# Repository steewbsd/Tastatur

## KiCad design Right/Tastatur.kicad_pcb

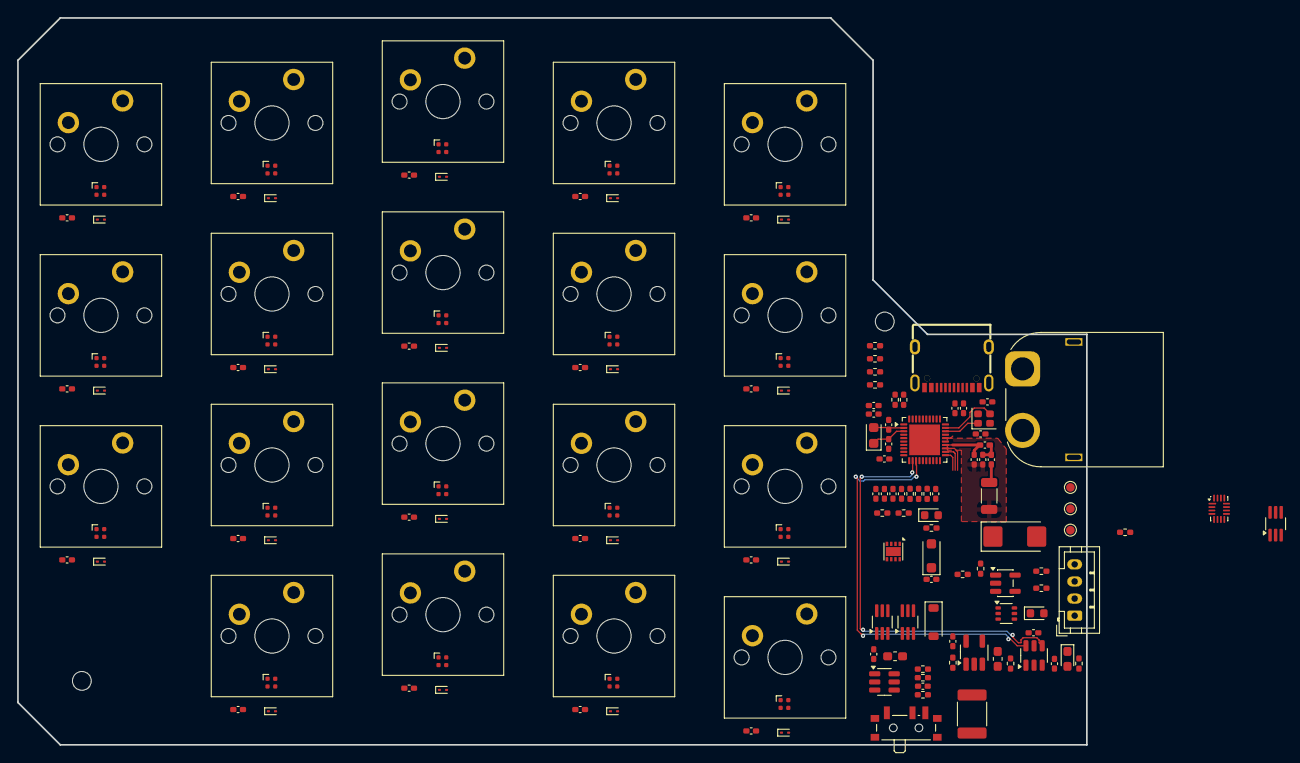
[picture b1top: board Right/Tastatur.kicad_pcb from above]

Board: 2 copper layers, 125.0 x 85.0 mm, 156 parts (1 on the bottom side), 103 nets.

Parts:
AE1: Antenna_Shield; L_1206_3216Metric
BT1: Battery_Cell; BatteryHolder_Keystone_1058_1x2032
C1, C37, C38, C39: 4u7; C_0402_1005Metric_Pad0.74x0.62mm_HandSolder
C2: 1u; C_0402_1005Metric_Pad0.74x0.62mm_HandSolder
C3: 100p; C_0402_1005Metric_Pad0.74x0.62mm_HandSolder
C4, C5, C14, C15, C16, C17, C18, C19, C20, C21, C22, C23, C24, C25, C26, C27, C28, C29, C30, C31, C32, C33, C34: 100n; C_0402_1005Metric_Pad0.74x0.62mm_HandSolder
C6, C9: 10p; C_0402_1005Metric_Pad0.74x0.62mm_HandSolder
C7, C8, C11: 22u; C_0402_1005Metric_Pad0.74x0.62mm_HandSolder
C10, C43: 10u; C_0402_1005Metric_Pad0.74x0.62mm_HandSolder
C13: 470u; CP_EIA-6032-28_Kemet-C_HandSolder
C35: 1p; C_0402_1005Metric_Pad0.74x0.62mm_HandSolder
C36: 802p; C_0402_1005Metric_Pad0.74x0.62mm_HandSolder
C40: 1p2; C_0402_1005Metric_Pad0.74x0.62mm_HandSolder
C41, C42: 12p; C_0402_1005Metric_Pad0.74x0.62mm_HandSolder
D1: CPDUR5V0HE-HF; D_0603_1608Metric_Pad1.05x0.95mm_HandSolder
D2: LMBR130T1G; D_SOD-123
D5: DDZ9678-7; D_SOD-123F
D6: RED; LED_0603_1608Metric
D7, D8, D9, D10, D11, D17, D18, D19, D20, D21, D27, D28, D29, D30, D31, D37, D38, D39, D40: SK6805-EC15; LED_SK6812_EC15_1.5x1.5mm
D12, D13, D14, D15, D16, D22, D23, D24, D25, D26, D32, D33, D34, D35, D36, D41, D42, D43, D44: RB521CS-30; D_SOD-923
D45: GREEN; LED_0603_1608Metric
F1: 1812L050/30PR; Fuse_1812_4532Metric_Pad1.30x3.40mm_HandSolder
H1, H2: MountingHole; MountingHole_2.2mm_M2_ISO7380
J1: Conn_01x04_Pin; JST_PH_B4B-PH-K_1x04_P2.00mm_Vertical
J3: XT60PW-M; AMASS_XT60PW-M_1x02_P7.20mm_Horizontal
L1: 4u7; L_0603_1608Metric_Pad1.05x0.95mm_HandSolder
L2: 120 Ohm @ 100 MHz; L_0603_1608Metric_Pad1.05x0.95mm_HandSolder
L3: 4n7; L_0402_1005Metric_Pad0.77x0.64mm_HandSolder
L4: 2n2; L_0402_1005Metric_Pad0.77x0.64mm_HandSolder
Q1, Q2, Q8: NTJD4152PT1G; SOT-363_SC-70-6_Handsoldering
Q3: Q_Dual_NMOS_S1G1D2S2G2D1; SOT-363_SC-70-6
R1, R25: 100R; R_0402_1005Metric_Pad0.72x0.64mm_HandSolder
R2, R10, R12: 50k; R_0402_1005Metric_Pad0.72x0.64mm_HandSolder
R3, R4: 5k1; R_0402_1005Metric_Pad0.72x0.64mm_HandSolder
R5, R28, R29: 0R; R_0402_1005Metric_Pad0.72x0.64mm_HandSolder
R6: 110k; R_0402_1005Metric_Pad0.72x0.64mm_HandSolder
R7: 15k; R_0402_1005Metric_Pad0.72x0.64mm_HandSolder
R13: 33k; R_0402_1005Metric_Pad0.72x0.64mm_HandSolder
R14: 51k; R_0402_1005Metric_Pad0.72x0.64mm_HandSolder
R15: 56k; R_0402_1005Metric_Pad0.72x0.64mm_HandSolder
R16, R17: 330R; R_0402_1005Metric_Pad0.72x0.64mm_HandSolder
R18: 20k; R_0402_1005Metric_Pad0.72x0.64mm_HandSolder
R21, R22, R23, R24: 500R; R_0402_1005Metric_Pad0.72x0.64mm_HandSolder
R26: 4k7; R_0402_1005Metric_Pad0.72x0.64mm_HandSolder
SW1: MK-12C02-G020; SW_SPDT_PCM12
SW2, SW3, SW4, SW5, SW6, SW7, SW8, SW9, SW10, SW11, SW12, SW13, SW14, SW15, SW16, SW17, SW18, SW19, SW20: SW_Push; SW_Cherry_MX_PCB_1.00u
TP1, TP2, TP3: TestPoint; TestPoint_Pad_D1.0mm
U1: USBLC6-2SC6; SOT-23-6
U2: TMUX1208RSV; UQFN-16_1.8x2.6mm_P0.4mm
U3: AP2112K-3.3; SOT-23-5_HandSoldering
U4: MT3608; SOT-23-6
U6: MCP73831-2-OT; SOT-23-5
U7: LM393; DFN-8-1EP_2x2mm_P0.5mm_EP1.05x1.75mm
U8: nRF52833_QDxx; QFN-40-1EP_5x5mm_P0.4mm_EP3.6x3.6mm
USB1: TYPE-C 16PIN 2MD(073); USB-C-SMD_TYPE-C-6PIN-2MD-073
Y1: 32MHz; Crystal_SMD_2016-4Pin_2.0x1.6mm
Y2: 32768 KHz; Crystal_SMD_2012-2Pin_2.0x1.2mm_HandSoldering

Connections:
+3V3: C1.2, C7.2, C13.1, C14.1, C38.2, C39.2, J1.2, L1.1, Q1.3 (D), Q1.6 (D), Q2.3 (D), R26.2, SW1.2 (C), U2.11 (VDD), U4.5 (IN), U8.8 (VDD), U8.9 (VDDH), U8.10 (VBUS), U8.18 (VDD), U8.30 (VDD), U8.40 (VDD)
+3V3BAT: Q1.1 (S), Q2.6 (D)
+3V3USB: C11.1, Q1.4 (S), Q3.1 (S), R12.2, TP3.1, U3.5 (VOUT)
+5V: C16.2, C17.2, C18.2, C19.2, C20.2, C21.2, C22.2, C23.2, C24.2, C25.2, C26.2, C27.2, C28.2, C29.2, C30.2, C31.2, C32.2, C33.2, C34.2, D7.4 (VDD), D8.4 (VDD), D9.4 (VDD), D10.4 (VDD), D11.4 (VDD), D17.4 (VDD), D18.4 (VDD), D19.4 (VDD), D20.4 (VDD), D21.4 (VDD), D27.4 (VDD), D28.4 (VDD), D29.4 (VDD), D30.4 (VDD), D31.4 (VDD), D37.4 (VDD), D38.4 (VDD), D39.4 (VDD), D40.4 (VDD), Q8.3 (D), Q8.6 (D)
+5VBAT: C8.2, D2.1 (K), Q8.1 (S), R6.1
+5VUSB: C43.2, F1.2, Q8.4 (S), R5.1, R16.1, TP2.1, U3.1 (VIN), U6.4 (V_{DD})
/COL0: SW2.1, SW7.1, SW12.1, U8.32 (AIN0/P0.02)
/COL1: SW3.1, SW8.1, SW13.1, SW17.1, U8.31 (AIN1/P0.03)
/COL2: SW4.1, SW9.1, SW14.1, SW18.1, U8.4 (AIN2/P0.04)
/COL3: SW5.1, SW10.1, SW15.1, SW19.1, U8.5 (AIN3/P0.05)
/COL4: SW6.1, SW11.1, SW16.1, SW20.1, U8.7 (P0.11)
/D+: U1.6 (I/O1), U8.13 (D+)
/D-: U1.4 (I/O2), U8.12 (D-)
/ED+: U1.1 (I/O1), USB1.6 (DP1), USB1.8 (DP2)
/ED-: U1.3 (I/O2), USB1.5 (DN2), USB1.7 (DN1)
/LD0: R21.1, U2.2 (S1)
/LD1: R22.1, U2.3 (S2)
/LD2: R23.1, U2.4 (S3)
/LD3: R24.1, U2.5 (S4)
/LEDDATA: U2.6 (D), U8.6 (P1.09)
/LEDSEL0: U2.15 (A0), U8.22 (NFC1/P0.09)
/LEDSEL1: U2.14 (A1), U8.23 (NFC2/P0.10)
/LEDTOGGLE: R2.1, SW1.1 (B), U2.16 (EN), U4.4 (EN)
/ROW0: D12.1 (K), D13.1 (K), D14.1 (K), D15.1 (K), D16.1 (K), U8.14 (P0.15)
/ROW1: D22.1 (K), D23.1 (K), D24.1 (K), D25.1 (K), D26.1 (K), U8.15 (P0.17)
/ROW2: D32.1 (K), D33.1 (K), D34.1 (K), D35.1 (K), D36.1 (K), U8.17 (P0.20)
/ROW3: D41.1 (K), D42.1 (K), D43.1 (K), D44.1 (K), U8.33 (AIN4/P0.28)
/VBAT: BT1.1 (+), C15.1, Q2.1 (S), Q3.2 (G), R10.2, R12.1, R13.1, R14.1, U6.3 (V_{BAT}), U7.8 (V+)
/VBUS: D1.2 (A2), L2.1, U1.5 (VBUS), USB1.2 (VBUS), USB1.11 (VBUS)
/mcu/SWDCLK: J1.4, R1.1
/mcu/SWDIO: J1.3, R25.1
GND: AE1.2 (Shield), BT1.2 (-), C1.1, C2.1, C3.1, C4.2, C5.1, C6.2, C7.1, C8.1, C9.2, C10.2, C11.2, C13.2, C14.2, C15.2, C16.1, C17.1, C18.1, C19.1, C20.1, C21.1, C22.1, C23.1, C24.1, C25.1, C26.1, C27.1, C28.1, C29.1, C30.1, C31.1, C32.1, C33.1, C34.1, C35.2, C36.1, C37.1, C38.1, C39.1, C40.2, C41.1, C42.1, C43.1, D1.1 (A1), D5.2 (A), D6.1 (K), D7.2 (VSS), D8.2 (VSS), D9.2 (VSS), D10.2 (VSS), D11.2 (VSS), D17.2 (VSS), D18.2 (VSS), D19.2 (VSS), D20.2 (VSS), D21.2 (VSS), D27.2 (VSS), D28.2 (VSS), D29.2 (VSS), D30.2 (VSS), D31.2 (VSS), D37.2 (VSS), D38.2 (VSS), D39.2 (VSS), D40.2 (VSS), J1.1, J3.2, Q1.2 (G), Q1.5 (G), Q2.5 (G), Q8.2 (G), Q8.5 (G), R2.2, R3.2, R4.2, R7.2, R15.2, R18.2, R28.2, R29.2, SW1.3 (A), TP1.1, U1.2 (GND), U2.1 (VSS), U2.12 (GND), U3.2 (GND), U4.2 (GND), U6.2 (V_{SS}), U7.4 (V-), U7.5 (+), U8.25 (VSS_PA), U8.37 (VSS), U8.41 (VSS), USB1.1 (GND), USB1.12 (GND), USB1.13 (SHELL), USB1.14 (SHELL), Y1.2, Y1.4
unnamed: AE1.1 (A), L4.1
unnamed: C10.1, F1.1, L2.2
unnamed: C40.1, L3.1, L4.2
unnamed: D2.2 (A), L1.2, U4.1 (SW)
unnamed: D5.1 (K), R14.2, U7.2 (-)
unnamed: D6.2 (A), R17.2
unnamed: D7.3 (DIN), R21.2
unnamed: D7.1 (DOUT), D8.3 (DIN)
unnamed: D8.1 (DOUT), D9.3 (DIN)
unnamed: D9.1 (DOUT), D10.3 (DIN)
unnamed: D10.1 (DOUT), D11.3 (DIN)
unnamed: D12.2 (A), SW2.2
unnamed: D13.2 (A), SW3.2
unnamed: D14.2 (A), SW4.2
unnamed: D15.2 (A), SW5.2
unnamed: D16.2 (A), SW6.2
unnamed: D17.3 (DIN), R22.2
unnamed: D17.1 (DOUT), D18.3 (DIN)
unnamed: D18.1 (DOUT), D19.3 (DIN)
unnamed: D19.1 (DOUT), D20.3 (DIN)
unnamed: D20.1 (DOUT), D21.3 (DIN)
unnamed: D22.2 (A), SW7.2
unnamed: D23.2 (A), SW8.2
unnamed: D24.2 (A), SW9.2
unnamed: D25.2 (A), SW10.2
unnamed: D26.2 (A), SW11.2
unnamed: D27.3 (DIN), R23.2
unnamed: D27.1 (DOUT), D28.3 (DIN)
unnamed: D28.1 (DOUT), D29.3 (DIN)
unnamed: D29.1 (DOUT), D30.3 (DIN)
unnamed: D30.1 (DOUT), D31.3 (DIN)
unnamed: D32.2 (A), SW12.2
unnamed: D33.2 (A), SW13.2
unnamed: D34.2 (A), SW14.2
unnamed: D35.2 (A), SW15.2
unnamed: D36.2 (A), SW16.2
unnamed: D37.3 (DIN), R24.2
unnamed: D37.1 (DOUT), D38.3 (DIN)
unnamed: D38.1 (DOUT), D39.3 (DIN)
unnamed: D39.1 (DOUT), D40.3 (DIN)
unnamed: D41.2 (A), SW17.2
unnamed: D42.2 (A), SW18.2
unnamed: D43.2 (A), SW19.2
unnamed: D44.2 (A), SW20.2
unnamed: D45.2 (A), R16.2
unnamed: D45.1 (K), U6.1 (STAT)
unnamed: J3.1, Q2.4 (S)
unnamed: Q2.2 (G), Q3.6 (D), R10.1
unnamed: R17.1, U7.1
unnamed: R5.2, U3.3 (EN)
unnamed: R6.2, R7.1, U4.3 (FB)
unnamed: R18.1, U6.5 (PROG)
unnamed: R13.2, R15.1, U7.3 (+)
unnamed: U7.6 (-), U7.7
unnamed: R29.1, U8.35 (AIN6/P0.30)
unnamed: R28.1, U8.36 (AIN7/P0.31)
unnamed: C35.1, L3.2, U8.24 (ANT)
unnamed: C5.2, U8.1 (DEC1)
unnamed: C3.2, U8.27 (DEC3)
unnamed: C2.2, U8.26 (DEC6), U8.38 (DEC4)
unnamed: C36.2, U8.21 (DEC5)
unnamed: C37.2, U8.11 (DECUSB)
unnamed: C4.1, R26.1, U8.16 (P0.18/~RESET)
unnamed: R1.2, U8.20 (SWDCLK)
unnamed: R25.2, U8.19 (SWDIO)
unnamed: C6.1, U8.28 (XC1), Y1.1
unnamed: C9.1, U8.29 (XC2), Y1.3
unnamed: C41.2, U8.2 (XL1/P0.00), Y2.2
unnamed: C42.2, U8.3 (XL2/P0.01), Y2.1
unnamed: R4.1, USB1.4 (CC1)
unnamed: R3.1, USB1.10 (CC2)

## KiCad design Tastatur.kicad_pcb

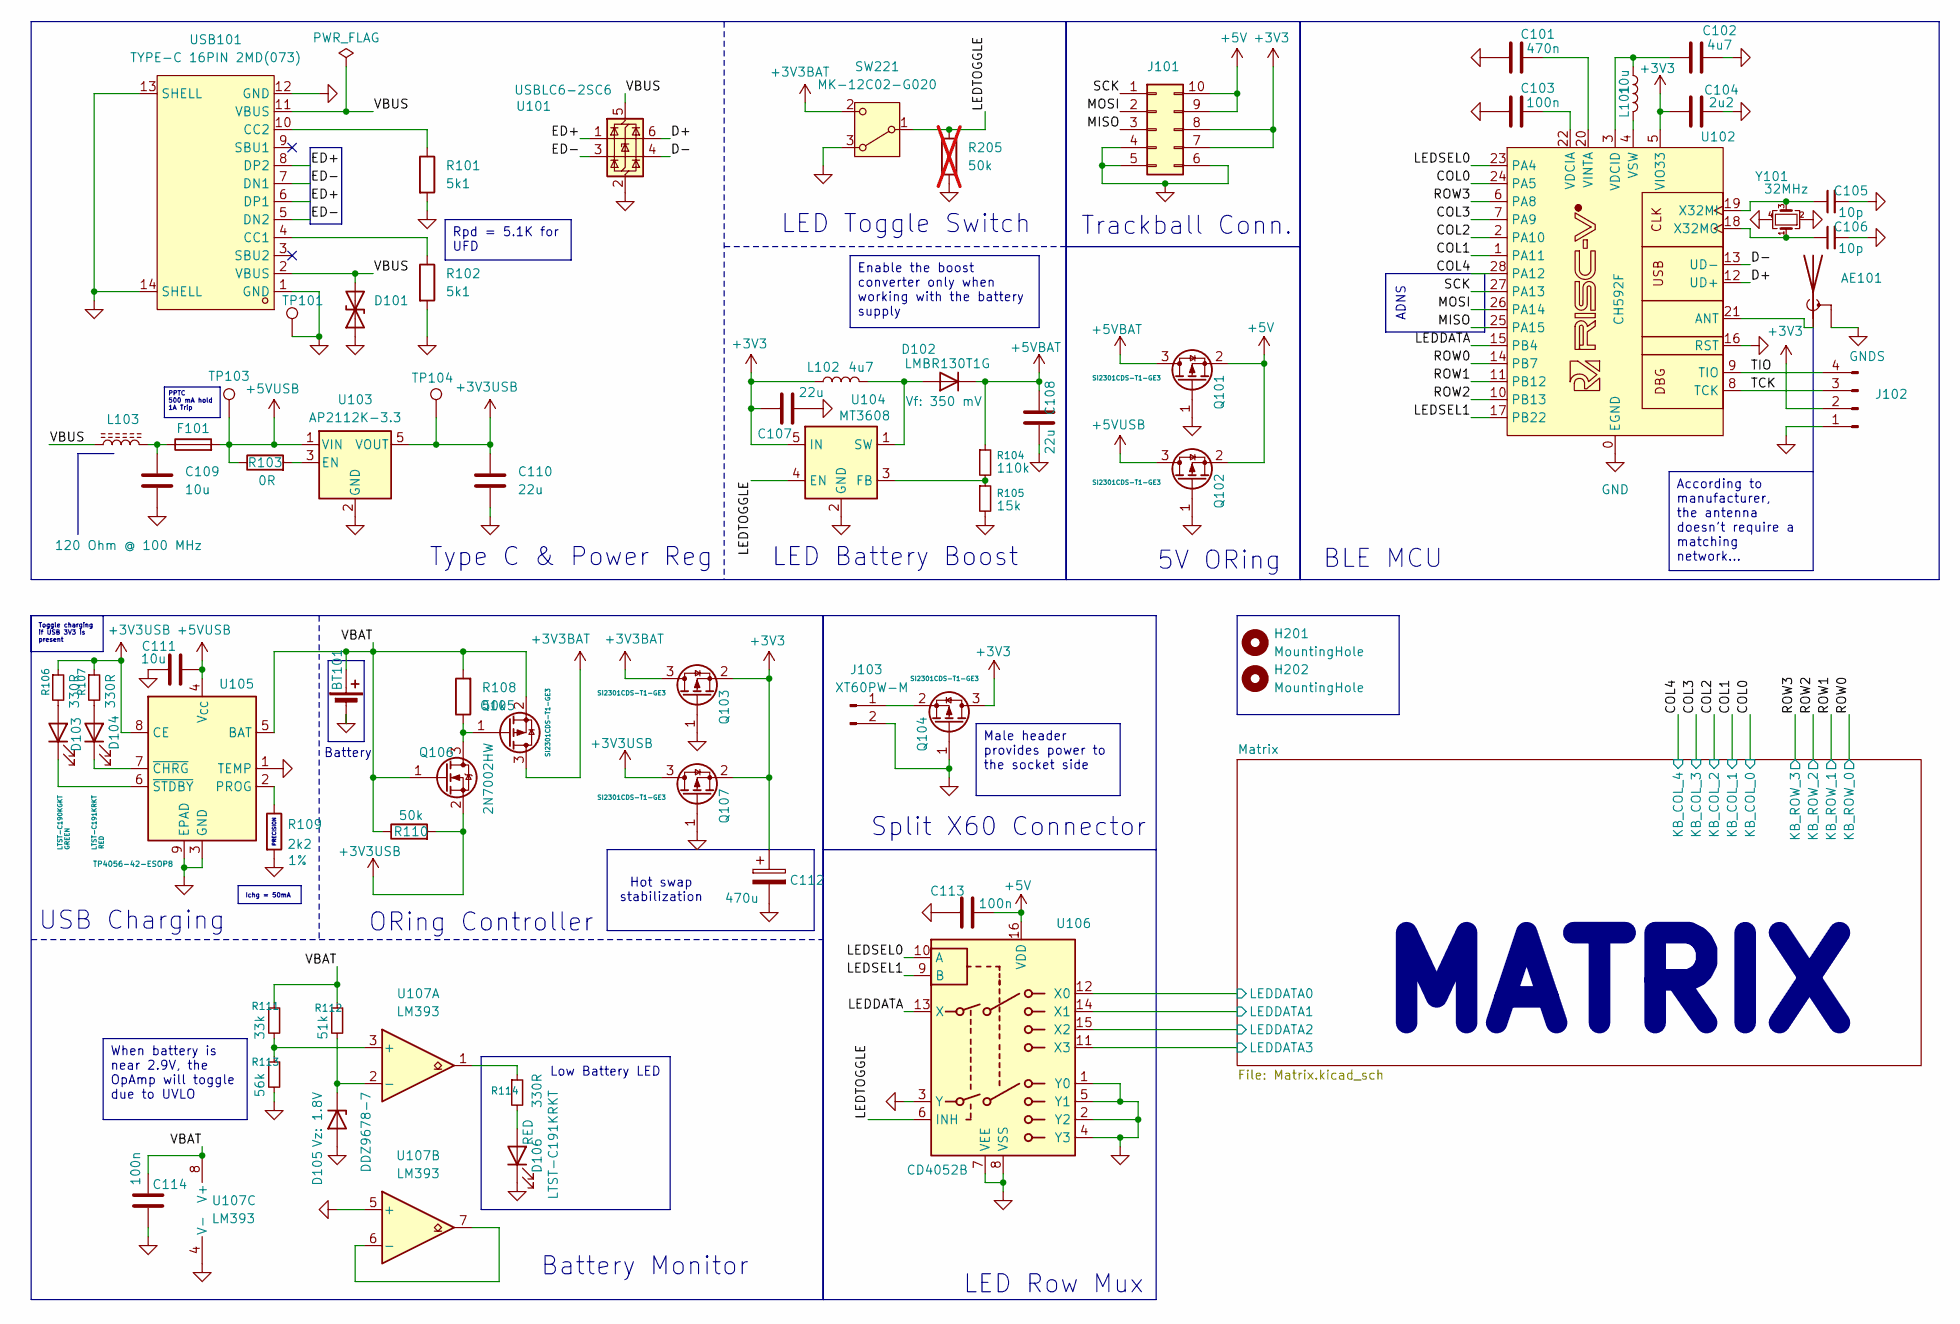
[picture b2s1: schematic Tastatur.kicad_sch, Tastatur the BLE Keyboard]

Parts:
AE101: Antenna_Shield; L_1206_3216Metric
BT101: Battery_Cell; BatteryHolder_Keystone_1058_1x2032
C101: 470n; C_0603_1608Metric_Pad1.08x0.95mm_HandSolder
C102: 4u7; C_0603_1608Metric_Pad1.08x0.95mm_HandSolder
C103, C113, C114: 100n; C_0603_1608Metric_Pad1.08x0.95mm_HandSolder
C104: 2u2; C_0603_1608Metric_Pad1.08x0.95mm_HandSolder
C105, C106: 10p; C_0603_1608Metric_Pad1.08x0.95mm_HandSolder
C107, C108, C110: 22u; C_0603_1608Metric_Pad1.08x0.95mm_HandSolder
C109, C111: 10u; C_0603_1608Metric_Pad1.08x0.95mm_HandSolder
C112: 470u; CP_Elec_6.3x7.7
D101: CPDUR5V0HE-HF; D_0603_1608Metric_Pad1.05x0.95mm_HandSolder
D102: LMBR130T1G; D_SOD-123
D103: GREEN; LED_0603_1608Metric
D104, D106: RED; LED_0603_1608Metric
D105: DDZ9678-7; D_SOD-123F
F101: 1812L050/30PR; Fuse_1812_4532Metric_Pad1.30x3.40mm_HandSolder
H201, H202: MountingHole; MountingHole_2.2mm_M2_ISO7380
J101: Conn_02x05_Counter_Clockwise
J102: Conn_01x04_Pin; JST_PH_B4B-PH-K_1x04_P2.00mm_Vertical
J103: XT60PW-M; AMASS_XT60PW-M_1x02_P7.20mm_Horizontal
L101: 10u; L_0603_1608Metric_Pad1.05x0.95mm_HandSolder
L102: 4u7; L_0603_1608Metric_Pad1.05x0.95mm_HandSolder
L103: 120 Ohm @ 100 MHz; L_0603_1608Metric_Pad1.05x0.95mm_HandSolder
Q101, Q102, Q103, Q104, Q105, Q107: SI2301CDS-T1-GE3; SOT-23_Handsoldering
Q106: 2N7002HW; SOT-323_SC-70_Handsoldering
R101, R102: 5k1; R_0603_1608Metric_Pad0.98x0.95mm_HandSolder
R103: 0R; R_0603_1608Metric_Pad0.98x0.95mm_HandSolder
R104: 110k; R_0603_1608Metric_Pad0.98x0.95mm_HandSolder
R105: 15k; R_0603_1608Metric_Pad0.98x0.95mm_HandSolder
R106, R107, R114: 330R; R_0603_1608Metric_Pad0.98x0.95mm_HandSolder
R108, R110: 50k; R_0603_1608Metric_Pad0.98x0.95mm_HandSolder
R109: 2k2; R_0603_1608Metric_Pad0.98x0.95mm_HandSolder; Tolerance 1%
R111: 33k; R_0603_1608Metric_Pad0.98x0.95mm_HandSolder
R112: 51k; R_0603_1608Metric_Pad0.98x0.95mm_HandSolder
R113: 56k; R_0603_1608Metric_Pad0.98x0.95mm_HandSolder
R205: 50k; R_0603_1608Metric_Pad0.98x0.95mm_HandSolder; not fitted
SW221: MK-12C02-G020; SW_SPDT_PCM12
TP101, TP103, TP104: TestPoint; TestPoint_Pad_D1.0mm
U101: USBLC6-2SC6; SOT-23-6
U102: CH592F
U103: AP2112K-3.3; SOT-23-5_HandSoldering
U104: MT3608; SOT-23-6
U105: TP4056-42-ESOP8; SOP-8-1EP_4.57x4.57mm_P1.27mm_EP4.57x4.45mm
U106: CD4052B; TSSOP-16_4.4x5mm_P0.65mm
U107: LM393; SOIC-8_3.9x4.9mm_P1.27mm
USB101: TYPE-C 16PIN 2MD(073); USB-C-SMD_TYPE-C-6PIN-2MD-073; LCSC Part C2765186
Y101: 32MHz; Crystal_SMD_2016-4Pin_2.0x1.6mm

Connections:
+3V3: C104.1, C107.2, C112.1, J101.7, J101.8, J102.2, L102.1, Q103.2 (S), Q104.3 (D), Q107.2 (S), U102.5 (VIO33), U104.5 (IN)
+3V3BAT: Q103.3 (D), Q105.3 (D), SW221.2 (C)
+3V3USB: C110.1, Q106.2 (S), Q107.3 (D), R106.1, R107.1, R110.2, TP104.1, U103.5 (VOUT), U105.8 (CE)
+5V: C113.1, J101.9, J101.10, Q101.2 (S), Q102.2 (S), U106.16 (VDD); also elsewhere on the board
+5VBAT: C108.2, D102.1 (K), Q101.3 (D), R104.1
+5VUSB: C111.2, F101.2, Q102.3 (D), R103.1, TP103.1, U103.1 (VIN), U105.4 (V_{CC})
/COL0: U102.24 (PA5); also elsewhere on the board
/COL1: U102.1 (PA11); also elsewhere on the board
/COL2: U102.2 (PA10); also elsewhere on the board
/COL3: U102.7 (PA9); also elsewhere on the board
/COL4: U102.28 (PA12); also elsewhere on the board
/D+: U101.6 (I/O1), U102.12 (UD+)
/D-: U101.4 (I/O2), U102.13 (UD-)
/ED+: U101.1 (I/O1), USB101.6 (DP1), USB101.8 (DP2)
/ED-: U101.3 (I/O2), USB101.5 (DN2), USB101.7 (DN1)
/LEDDATA: U102.15 (PB4), U106.13 (X)
/LEDSEL0: U102.23 (PA4), U106.10 (A)
/LEDSEL1: U102.17 (PB22), U106.9 (B)
/LEDTOGGLE: R205.1, SW221.1 (B), U104.4 (EN), U106.6 (INH)
/MISO: J101.3, U102.25 (PA15)
/MOSI: J101.2, U102.26 (PA14)
/Matrix/LEDDATA0: U106.12 (X0); also elsewhere on the board
/Matrix/LEDDATA1: U106.14 (X1); also elsewhere on the board
/Matrix/LEDDATA2: U106.15 (X2); also elsewhere on the board
/Matrix/LEDDATA3: U106.11 (X3); also elsewhere on the board
/ROW0: U102.14 (PB7); also elsewhere on the board
/ROW1: U102.11 (PB12); also elsewhere on the board
/ROW2: U102.10 (PB13); also elsewhere on the board
/ROW3: U102.6 (PA8); also elsewhere on the board
/SCK: J101.1, U102.27 (PA13)
/TCK: J102.3, U102.8 (TCK)
/TIO: J102.4, U102.9 (TIO)
/VBAT: BT101.1 (+), C114.1, Q105.2 (S), Q106.1 (G), R108.2, R110.1, R111.1, R112.1, U105.5 (BAT), U107.8 (V+)
/VBUS: D101.2 (A2), L103.1, U101.5 (VBUS), USB101.2 (VBUS), USB101.11 (VBUS)
GND: BT101.2 (-), C101.1, C102.2, C103.1, C104.2, C105.2, C106.2, C107.1, C108.1, C109.2, C110.2, C111.1, C112.2, C113.2, C114.2, D101.1 (A1), D105.2 (A), D106.1 (K), J101.4, J101.5, J101.6, J102.1, J103.2, Q101.1 (G), Q102.1 (G), Q103.1 (G), Q104.1 (G), Q107.1 (G), R101.2, R102.2, R105.2, R109.2, R113.2, R205.2, SW221.3 (A), TP101.1, U101.2 (GND), U102.0 (EGND), U102.16 (RST), U103.2 (GND), U104.2 (GND), U105.1 (TEMP), U105.3 (GND), U105.9 (EPAD), U106.1 (Y0), U106.2 (Y2), U106.3 (Y), U106.4 (Y3), U106.5 (Y1), U106.7 (VEE), U106.8 (VSS), U107.4 (V-), U107.5 (+), USB101.1 (GND), USB101.12 (GND), USB101.13 (SHELL), USB101.14 (SHELL), Y101.2, Y101.4; also elsewhere on the board
GNDS: AE101.2 (Shield)
unnamed: AE101.1 (A), U102.21 (ANT)
unnamed: C109.1, F101.1, L103.2
unnamed: D102.2 (A), L102.2, U104.1 (SW)
unnamed: D103.2 (A), R106.2
unnamed: D103.1 (K), U105.6 (~STDBY)
unnamed: D104.2 (A), R107.2
unnamed: D104.1 (K), U105.7 (~CHRG)
unnamed: D105.1 (K), R112.2, U107.2 (-)
unnamed: D106.2 (A), R114.2
unnamed: J103.1, Q104.2 (S)
unnamed: Q105.1 (G), Q106.3 (D), R108.1
unnamed: R114.1, U107.1
unnamed: C103.2, U102.22 (VDCIA)
unnamed: C102.1, L101.1, U102.3 (VDCID)
unnamed: C101.2, U102.20 (VINTA)
unnamed: L101.2, U102.4 (VSW)
unnamed: C105.1, U102.19 (X32MI), Y101.3
unnamed: C106.1, U102.18 (X32MO), Y101.1
unnamed: R103.2, U103.3 (EN)
unnamed: R104.2, R105.1, U104.3 (FB)
unnamed: R109.1, U105.2 (PROG)
unnamed: R111.2, R113.1, U107.3 (+)
unnamed: U107.6 (-), U107.7
unnamed: R102.1, USB101.4 (CC1)
unnamed: R101.1, USB101.10 (CC2)

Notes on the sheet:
LED Toggle Switch
Hot swap stabilization
MATRIX
PRECISION
Low Battery LED
5V ORing
USB Charging
BLE MCU
Battery
ADNS
Split X60 Connector
Battery Monitor
ORing Controller
Trackball Conn.
LED Battery Boost
Type C & Power Reg
LED Row Mux
According to manufacturer, the antenna doesn't require a matching network...
Ichg = 50mA
PPTC 500 mA hold 1A Trip
Toggle charging if USB 3V3 is present
When battery is near 2.9V, the OpAmp will toggle due to UVLO
Enable the boost converter only when working with the battery supply
Male header provides power to the socket side
Rpd = 5.1K for UFD

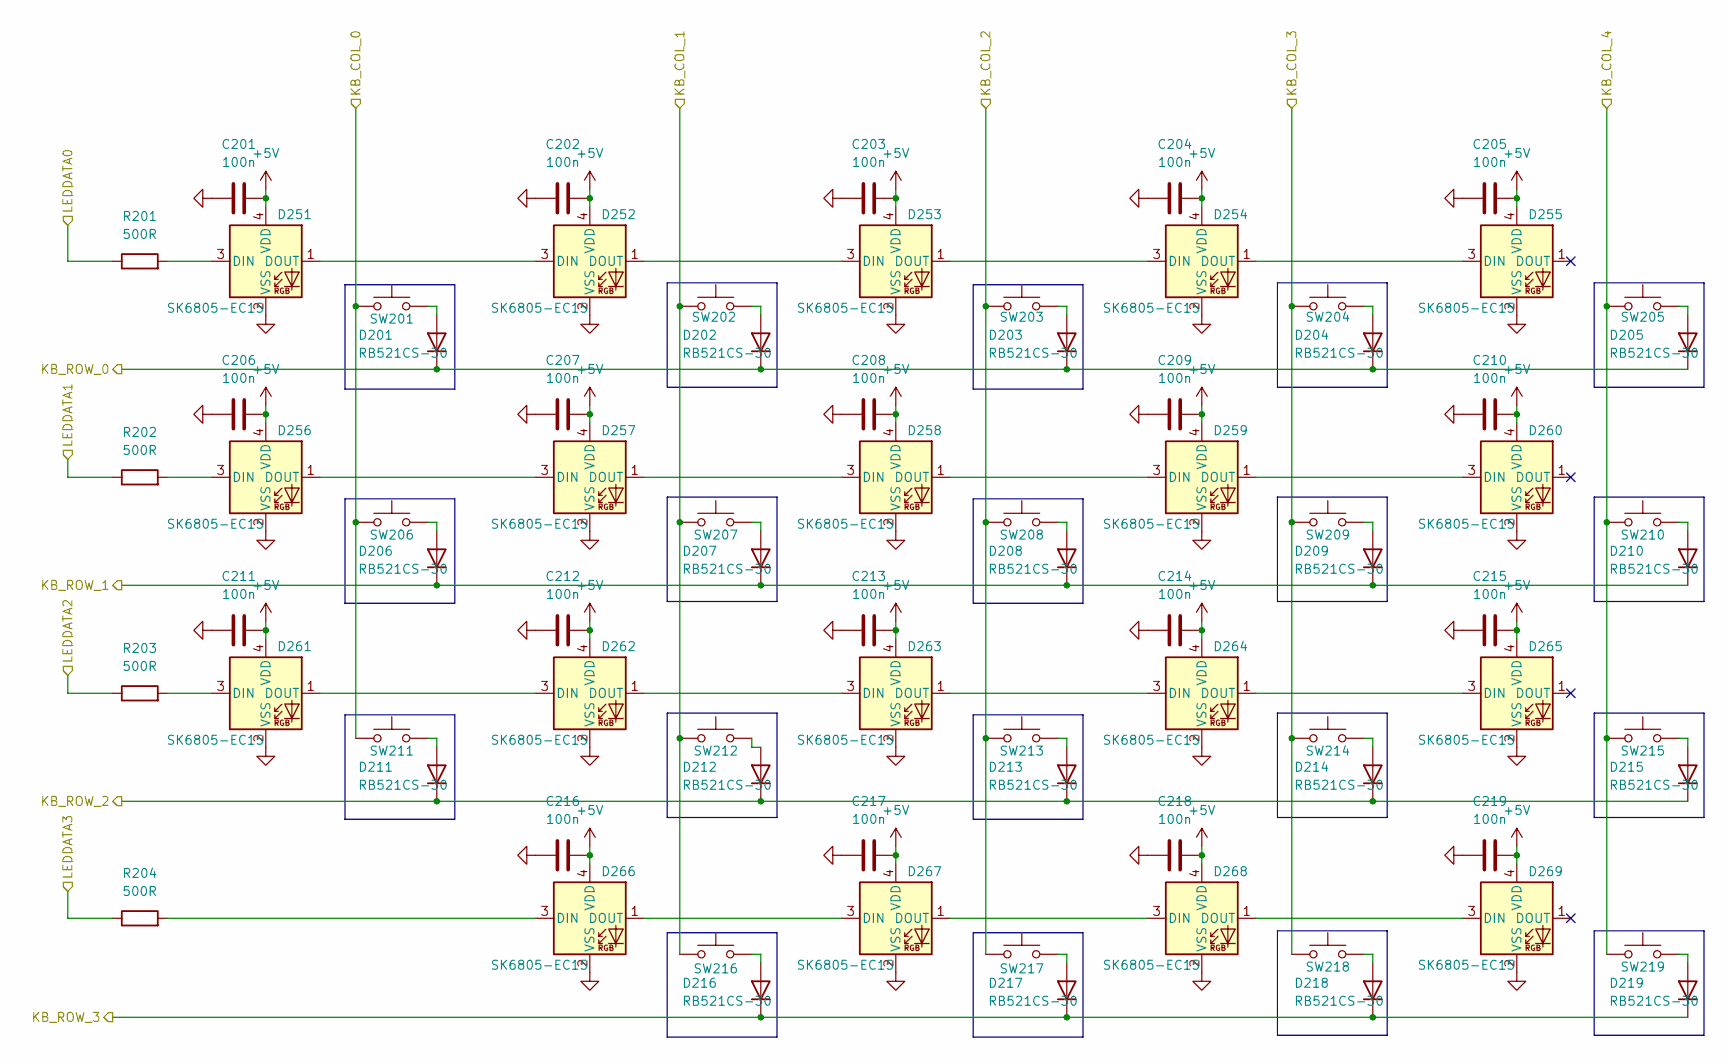
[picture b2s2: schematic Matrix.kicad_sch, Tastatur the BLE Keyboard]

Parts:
C201, C202, C203, C204, C205, C206, C207, C208, C209, C210, C211, C212, C213, C214, C215, C216, C217, C218, C219: 100n; C_0603_1608Metric_Pad1.08x0.95mm_HandSolder
D201, D202, D203, D204, D205, D206, D207, D208, D209, D210, D211, D212, D213, D214, D215, D216, D217, D218, D219: RB521CS-30; D_SOD-923
D251, D252, D253, D254, D255, D256, D257, D258, D259, D260, D261, D262, D263, D264, D265, D266, D267, D268, D269: SK6805-EC15; LED_SK6812_EC15_1.5x1.5mm; LCSC C2890035
R201, R202, R203, R204: 500R; R_0603_1608Metric_Pad0.98x0.95mm_HandSolder
SW201, SW202, SW203, SW204, SW205, SW206, SW207, SW208, SW209, SW210, SW211, SW212, SW213, SW214, SW215, SW216, SW217, SW218, SW219: SW_Push; SW_Cherry_MX_PCB_1.00u

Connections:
+5V: C201.2, C202.2, C203.2, C204.2, C205.2, C206.2, C207.2, C208.2, C209.2, C210.2, C211.2, C212.2, C213.2, C214.2, C215.2, C216.2, C217.2, C218.2, C219.2, D251.4 (VDD), D252.4 (VDD), D253.4 (VDD), D254.4 (VDD), D255.4 (VDD), D256.4 (VDD), D257.4 (VDD), D258.4 (VDD), D259.4 (VDD), D260.4 (VDD), D261.4 (VDD), D262.4 (VDD), D263.4 (VDD), D264.4 (VDD), D265.4 (VDD), D266.4 (VDD), D267.4 (VDD), D268.4 (VDD), D269.4 (VDD); also elsewhere on the board
/COL0: SW201.1, SW206.1, SW211.1; also elsewhere on the board
/COL1: SW202.1, SW207.1, SW212.1, SW216.1; also elsewhere on the board
/COL2: SW203.1, SW208.1, SW213.1, SW217.1; also elsewhere on the board
/COL3: SW204.1, SW209.1, SW214.1, SW218.1; also elsewhere on the board
/COL4: SW205.1, SW210.1, SW215.1, SW219.1; also elsewhere on the board
/Matrix/LEDDATA0: R201.1; also elsewhere on the board
/Matrix/LEDDATA1: R202.1; also elsewhere on the board
/Matrix/LEDDATA2: R203.1; also elsewhere on the board
/Matrix/LEDDATA3: R204.1; also elsewhere on the board
/ROW0: D201.1 (K), D202.1 (K), D203.1 (K), D204.1 (K), D205.1 (K); also elsewhere on the board
/ROW1: D206.1 (K), D207.1 (K), D208.1 (K), D209.1 (K), D210.1 (K); also elsewhere on the board
/ROW2: D211.1 (K), D212.1 (K), D213.1 (K), D214.1 (K), D215.1 (K); also elsewhere on the board
/ROW3: D216.1 (K), D217.1 (K), D218.1 (K), D219.1 (K); also elsewhere on the board
GND: C201.1, C202.1, C203.1, C204.1, C205.1, C206.1, C207.1, C208.1, C209.1, C210.1, C211.1, C212.1, C213.1, C214.1, C215.1, C216.1, C217.1, C218.1, C219.1, D251.2 (VSS), D252.2 (VSS), D253.2 (VSS), D254.2 (VSS), D255.2 (VSS), D256.2 (VSS), D257.2 (VSS), D258.2 (VSS), D259.2 (VSS), D260.2 (VSS), D261.2 (VSS), D262.2 (VSS), D263.2 (VSS), D264.2 (VSS), D265.2 (VSS), D266.2 (VSS), D267.2 (VSS), D268.2 (VSS), D269.2 (VSS); also elsewhere on the board
unnamed: D201.2 (A), SW201.2
unnamed: D202.2 (A), SW202.2
unnamed: D203.2 (A), SW203.2
unnamed: D204.2 (A), SW204.2
unnamed: D205.2 (A), SW205.2
unnamed: D206.2 (A), SW206.2
unnamed: D207.2 (A), SW207.2
unnamed: D208.2 (A), SW208.2
unnamed: D209.2 (A), SW209.2
unnamed: D210.2 (A), SW210.2
unnamed: D211.2 (A), SW211.2
unnamed: D212.2 (A), SW212.2
unnamed: D213.2 (A), SW213.2
unnamed: D214.2 (A), SW214.2
unnamed: D215.2 (A), SW215.2
unnamed: D216.2 (A), SW216.2
unnamed: D217.2 (A), SW217.2
unnamed: D218.2 (A), SW218.2
unnamed: D219.2 (A), SW219.2
unnamed: D251.3 (DIN), R201.2
unnamed: D251.1 (DOUT), D252.3 (DIN)
unnamed: D252.1 (DOUT), D253.3 (DIN)
unnamed: D253.1 (DOUT), D254.3 (DIN)
unnamed: D254.1 (DOUT), D255.3 (DIN)
unnamed: D256.3 (DIN), R202.2
unnamed: D256.1 (DOUT), D257.3 (DIN)
unnamed: D257.1 (DOUT), D258.3 (DIN)
unnamed: D258.1 (DOUT), D259.3 (DIN)
unnamed: D259.1 (DOUT), D260.3 (DIN)
unnamed: D261.3 (DIN), R203.2
unnamed: D261.1 (DOUT), D262.3 (DIN)
unnamed: D262.1 (DOUT), D263.3 (DIN)
unnamed: D263.1 (DOUT), D264.3 (DIN)
unnamed: D264.1 (DOUT), D265.3 (DIN)
unnamed: D266.3 (DIN), R204.2
unnamed: D266.1 (DOUT), D267.3 (DIN)
unnamed: D267.1 (DOUT), D268.3 (DIN)
unnamed: D268.1 (DOUT), D269.3 (DIN)

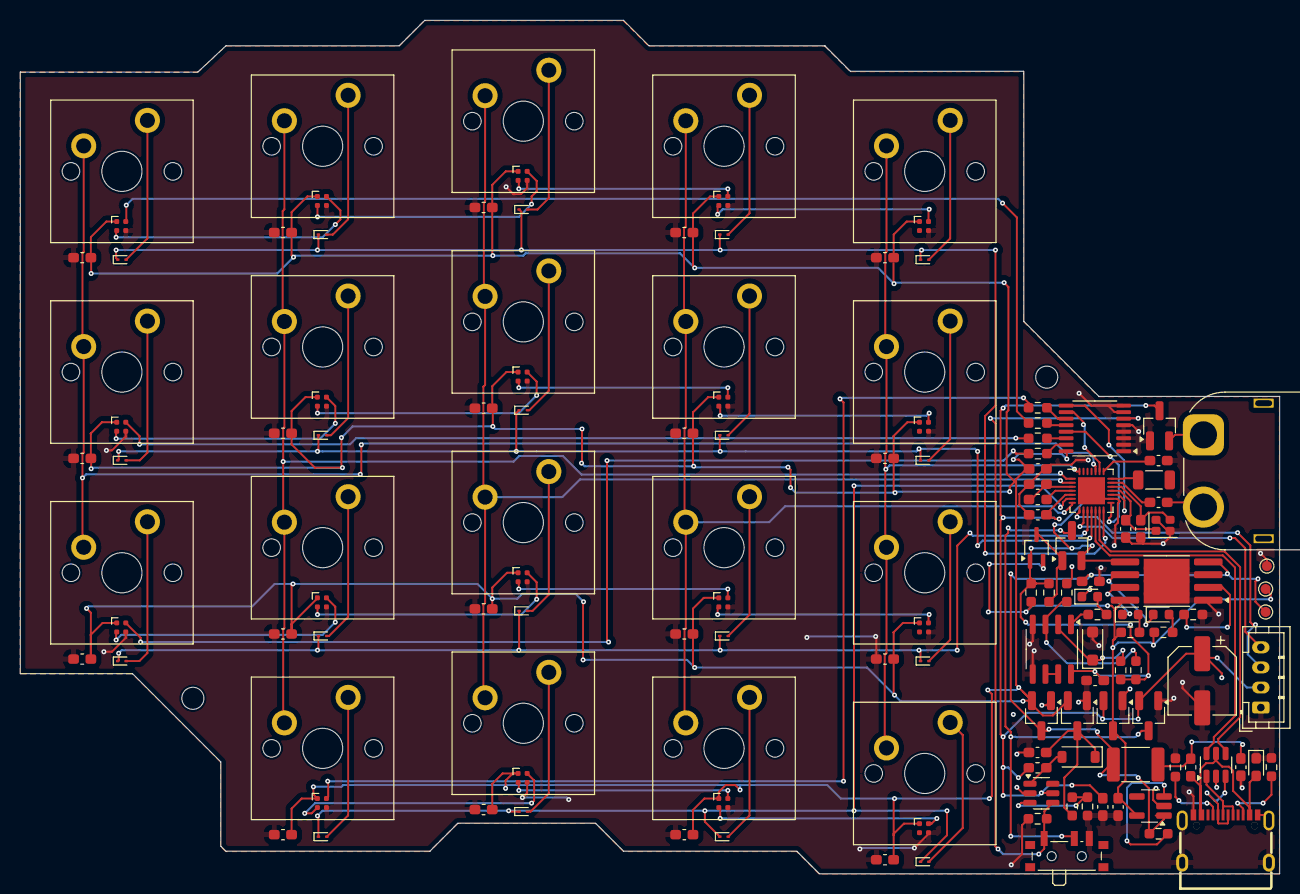
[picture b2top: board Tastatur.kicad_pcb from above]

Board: 2 copper layers, 125.5 x 85.1 mm, 145 parts (1 on the bottom side), 95 nets.

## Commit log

2025-07-13 update power mgmt
2025-07-13 add pdf
2025-07-18 finish preliminary schematic
2025-07-18 amend UVLO values
2025-07-25 finish initial placement
2025-07-27 start routing power
2025-07-30 halfway new routing
2025-08-01 final routing
2025-11-28 Update latest revisio
2025-12-08 update design to use CH582F
2026-03-31 redesign with smaller components
